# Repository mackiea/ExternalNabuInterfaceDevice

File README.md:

# External Nabu Interface Device (ENID-25)

A simple way to export the NABU's option card to via a common DB interface. Almost all pins map exactly from the NABU Option Card specification to the DB-25 pins, with the exception of the power pins.
The ENID is meant to take the place of a NABU Option Card Plate. Each NABU has 4 removable metal plates to allow for external interface and access to any  Option Cards installed. These plates correspond to 4 30-pin Option Card interface mounted on the board.

# Why?
I wanted to extend the abilities of the NABU. The most convenient way of doing this without disrupting the main system is to make use of the Option Card bus -- a series of 4 30-pin connectors on the motherboard that allow for the addition of peripherals and hardware extensions. My issues:
  - I want to keep internal access to a minimum -- ideally, connect up to all 4 slots to ENIDS, then button up the NABU.
  - I do not want to cut into the Option Card Plates -- leaving them intact, as the NABU is a collectible item with limited parts availability.
  - I want to add protection by both limiting the exposed power access to a fusable 5V rail, and keeping the +12V and -12V rails disconnected.
  - I want a widely adopted interface connector. DB-25 is very popular for legacy serial and parallel PC interfacing, and cheaply available on electronics supply sites.

# Applications
- [BEAVER Boarduino Adaptor](https://github.com/mackiea/BasicEnidArduinoValidationExchangeRrrr) to allow for testing and peripheral prototyping.
- PC Gameport -- TBA - To support [Gameport](https://en.wikipedia.org/wiki/Game_port) joystick and peripheral input.
- RC2014 adaptor -- TBA - To support [RC2014] (https://rc2014.co.uk) peripherals.

# Output Connector
The DB-25 is a 25-pin interface, used in many applications, primarily RS-232 serial and PC parallel cabling. When selecting a cable or connector, care should be taken to select one where all pins are connected -- some serial cables may have only a few pins connected (RX/TX, DTS/RTS, etc).

# Differences
Since the DB-25 connector has 5 less signals available than the NABU Option Card interface exposes, the following are not propagated:
- +5V rail 2
- Ground rails 2 & 3
- +12V rail
- -12V rail

As well, ground rail 1 is redirected from NABU pin 26 to DB-25 pin 25, as per the Pinout table.

The connected +5V rail can be connected either directly (not recommended) or connected to a fuse with a 1x2 electrical jumper. The specifications call for a ~1A resettable LittleFuse-brand fuse, but other fuses can be used, if their leads fit in themsoldering holes.

# Notes
- Ensure that the cable used is not a null-cable or loopback-cable. You can tell if pin 2 (RS-232 Receive) and pin 3 (RS-232 Transmit) are switched at each end using a multimeter.
- Connecting and disconnecting the DB-25 cable exerts a considerable force on the ENID. It is recommended to add a non-conductive reinforcement across the 2 Option Card Plate bolts.
- The 2 1x13 connectors on the ENID card (JOP1 & JOP2) should be male, as the card is receiving power. JFUSE1 (1x3) should also be male to accommodate a jumper to select the power mode.
- The BOM calls for 2 1x13 0.1"(2.56mm)-pitch cables, female on both ends.

# Caveats
- The existing Option Card plate screws will not suffice to hold the ENID card in. Upgrade to a pair of fitting bolts and nuts.
- The PCB is connected to the NABU as a plate by 2 bolts. Use of this involves plugging in a DB-25 connector, which exerts a considerable force on the board. I highly recommend sandwiching the PCB with a nonconductive backing material behind it, on the same bolts, to take the strain of the plugging. I also recommend providing counterstrain to the female DB-25's tabs when plugging a male DB-25 connector in.
- This is NOT a direct parallel or serial interface. Trying to connect devices as such won't work without an intermediary device, and may harm your NABU, external device, or self-esteem.
- Mind how you plug the 1x13 Connectors into the Options Card pins. They plug into pins 1-13 and 14-26. 27-30 should not be connected. Especially considering that Pins 29 & 30 may be +12 and -12 volts respectively. I'll add pictures and video once I start adding boards. NABU Option Card pin 1 appears to be the furthest back in the NABU enclosure.

# Pinout
ENID's pinout should map almost exactly to the Option Card pinout, with the exception of the first ground rail NABU pin 26, which on the ENID is pin 25; and of course, NABU pins 25 & 27-30 are not propagated.

## ENID Pins
| ENID DB-25 | Input from NABU | Description |
| ---------- | --------------- | ----------- |
| 1 | 1 | Interrupt |
| 2 | 2 | Interrupt Acknowledge |
| 3 | 3 | 3.58 MHz Clock |
| 4 | 4 | Audio |
| 5 | 5 | Chip Select |
| 6 | 6 | Address 0 |
| 7 | 7 | Address 1 |
| 8 | 8 | Address 2 |
| 9 | 9 | Address 3 |
| 10 | 10 | 1.79 MHz Clock |
| 11 | 11 | Write |
| 12 | 12 | Read |
| 13 | 13 | I/O Request |
| 14 | 14 | Wait |
| 15 | 15 | Reset |
| 16 | 16 | Data 0 |
| 17 | 17 | Data 1 |
| 18 | 18 | Data 2 |
| 19 | 19 | Data 3 |
| 20 | 20 | Data 4 |
| 21 | 21 | Data 5 |
| 22 | 22 | Data 6 |
| 23 | 23 | Data 7 |
| 24 | 24 | +5V Rail 1 |
| 25 | 26 | Ground Rail 1 |

## Unused pins
| Input from NABU | Description |
| --------------- | ----------- |
| 25 | +5V Rail 2 |
| 27 | Ground Rail 2 |
| 28 | Ground Rail 3 |
| 29 | +12V Rail |
| 30 | -12V Rail |

# Concerns
- The board is anchored to the NABU box by 2 bolts. There is no reinforcement for the RS-232 connector. There is a concern that over time the stress of plugging & unplugging the connector will cause the PCB to crack from the forces required. PCBs ordered should have a composition and thickness as high as can be reasonably ordered (don't cheap out). Alternatively, a non-conducting reinforcement bar can be layered behind the PCB, connecting to the aforementioned bolts, but able to absorb the strain imparted by connecting a DB-25 connector.
- The DB-25 connector, in general, is used in serial and parallel applications. None are compatible with ENID. Attempting to connect this to a serial or parallel device will very possibly cause some magic smoke to spew out. However, this is designed to be a springboard to add adapters to connect to various devices using new or existing PCBs or microcontrollers. 

# More information
http://www.nabu.ca

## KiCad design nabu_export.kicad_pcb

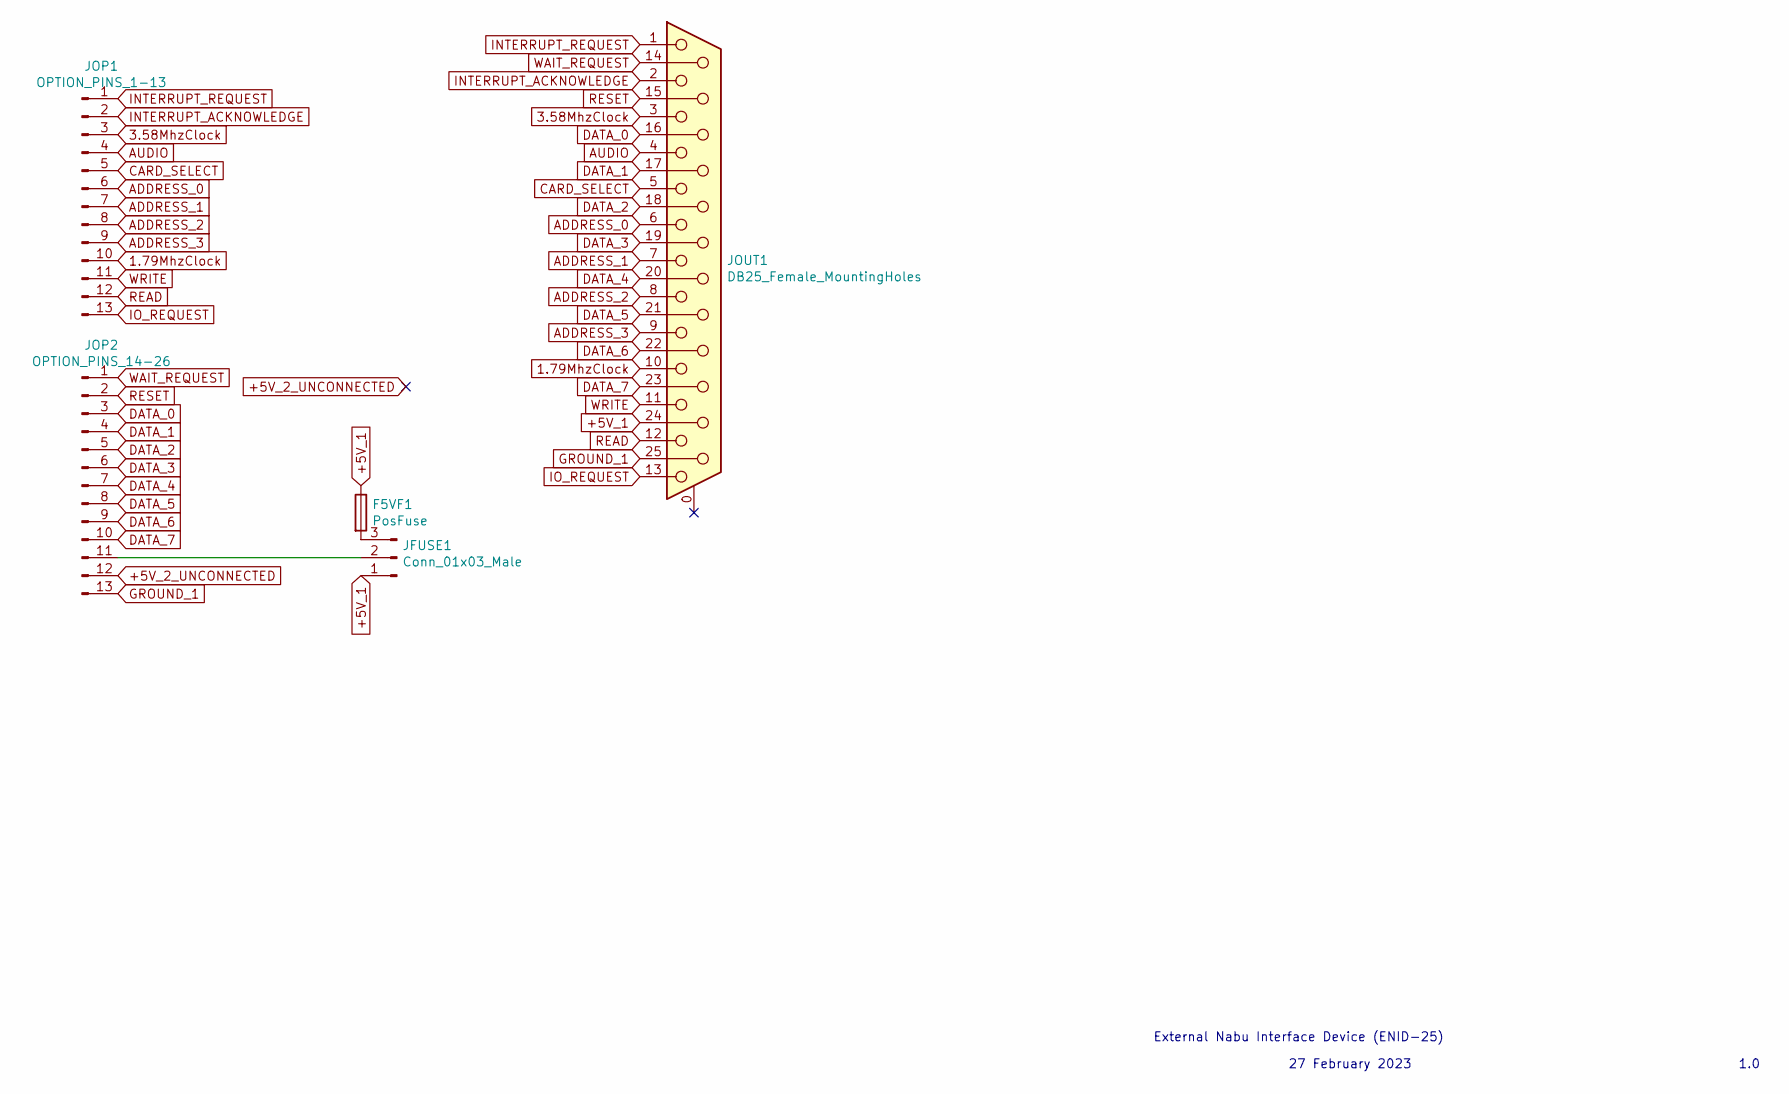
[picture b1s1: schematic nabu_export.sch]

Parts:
F5VF1: PosFuse; Fuse_Littelfuse-LVR100
JFUSE1: Conn_01x03_Male; PinHeader_1x03_P2.54mm_Vertical
JOP1: OPTION_PINS_1-13; PinHeader_1x13_P2.54mm_Vertical
JOP2: OPTION_PINS_14-26; PinHeader_1x13_P2.54mm_Vertical
JOUT1: DB25_Female_MountingHoles; DSUB-25_Female_Vertical_P2.77x2.84mm_MountingHoles

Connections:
1.79MhzClock: JOP1.10, JOUT1.10
3.58MhzClock: JOP1.3, JOUT1.3
+5V_1: F5VF1.1, JFUSE1.1, JOUT1.24
+5V_2_UNCONNECTED: JOP2.12
ADDRESS_0: JOP1.6, JOUT1.6
ADDRESS_1: JOP1.7, JOUT1.7
ADDRESS_2: JOP1.8, JOUT1.8
ADDRESS_3: JOP1.9, JOUT1.9
AUDIO: JOP1.4, JOUT1.4
CARD_SELECT: JOP1.5, JOUT1.5
DATA_0: JOP2.3, JOUT1.16
DATA_1: JOP2.4, JOUT1.17
DATA_2: JOP2.5, JOUT1.18
DATA_3: JOP2.6, JOUT1.19
DATA_4: JOP2.7, JOUT1.20
DATA_5: JOP2.8, JOUT1.21
DATA_6: JOP2.9, JOUT1.22
DATA_7: JOP2.10, JOUT1.23
GROUND_1: JOP2.13, JOUT1.25
INTERRUPT_ACKNOWLEDGE: JOP1.2, JOUT1.2
INTERRUPT_REQUEST: JOP1.1, JOUT1.1
IO_REQUEST: JOP1.13, JOUT1.13
unnamed: F5VF1.2, JFUSE1.3
unnamed: JFUSE1.2, JOP2.11
READ: JOP1.12, JOUT1.12
RESET: JOP2.2, JOUT1.15
WAIT_REQUEST: JOP2.1, JOUT1.14
WRITE: JOP1.11, JOUT1.11

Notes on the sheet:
External Nabu Interface Device (ENID-25)
1.0
27 February 2023

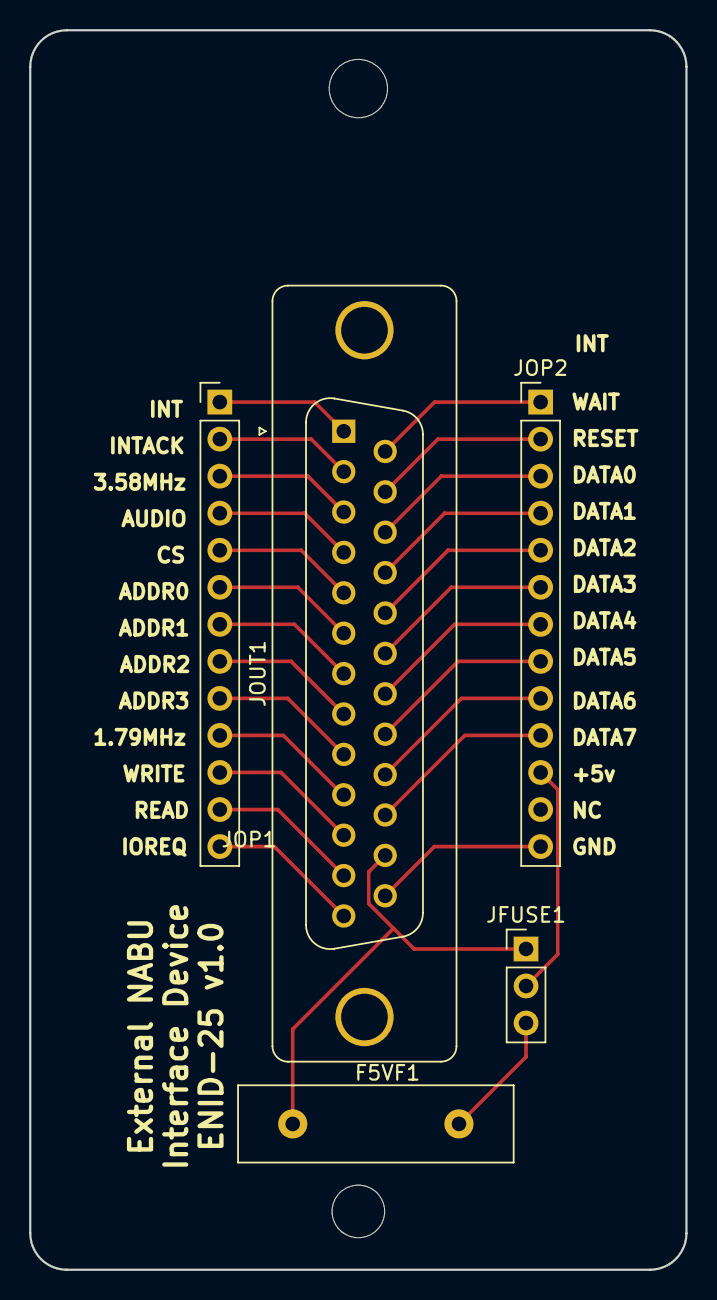
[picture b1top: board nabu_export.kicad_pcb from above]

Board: 2 copper layers, 45.0 x 85.0 mm, 5 parts (0 on the bottom side), 27 nets.

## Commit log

2023-02-27 First addition of files for ENID-25 (DB-25 interface).
2023-03-01 Added reference images.
2023-03-22 Added images proving the boards exist :)
2023-03-22 Rotated image
